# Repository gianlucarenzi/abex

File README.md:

Atari Bus EXtender for Atari XE Computers
=====================================

This is a Atari PBI & ECI Bus extender, for adding expansion board with ease,
called Atari Bus EXtender for Atari XE Computers or ABEX for short.

This project expand somehow the Atari 1090XL Bus Expansion in the early 80s
but with a simple layout and using only 3.3v compliant electronics.
No 5V is available on the bus, and all signals are converted to 3.3v level.

The Bus recall somehow the AteoBus from Amiga 1200 Computers but using a
more common nowadays PCI-Express Bus Slots with 64 pins.

Right now there are 2 boards desinged for this bus:

1- Atari DUO Cart (a porting of the famous Uno-Cart Project)

2- Atari MegaRAM (a PortB PIA Emulator) with 1024K RAM memory banked

More boards can be added as soon they do not interfere with the others
like using the PBI Protocol device in available in ROM. For example a simple
RS232 Board can be designed using a STM32F407 as port EXPANDER with R: handler
in internal flash, or a SDCard Hard Drive Simulator can be designed as well.

Even WiFi or Ethernet Controller can be achived flawlessly.

Everything is up to you, using your mind to open the world to this wonderful
machine like Atari 130XE.

Rendered Images
===============
# Front
# Back
# Overall

Hardware License
================
Copyright (C) 2018/2019 Gianluca Renzi <gianlucarenzi@eurek.it> <icjtqr@gmail.com>

The hardware of this project is released as free/open hardware under the
Creative Commons Attribution Share-Alike license. See `LICENSE.hw` for details.

Firmware License
================
Copyright (C) 2019 Gianluca Renzi <icjtqr@gmail.com>

The microcontroller firmware of this project is released as free software,
under the terms of the GNU General Public License v3, or later.  See
`LICENSE.sw` for details.

Software License
================
The host software (amigafloppy tool) is released as free software, under the
terms of the GNU General Public License v3, or later. See `LICENSE.sw` or licence.txt for
details.

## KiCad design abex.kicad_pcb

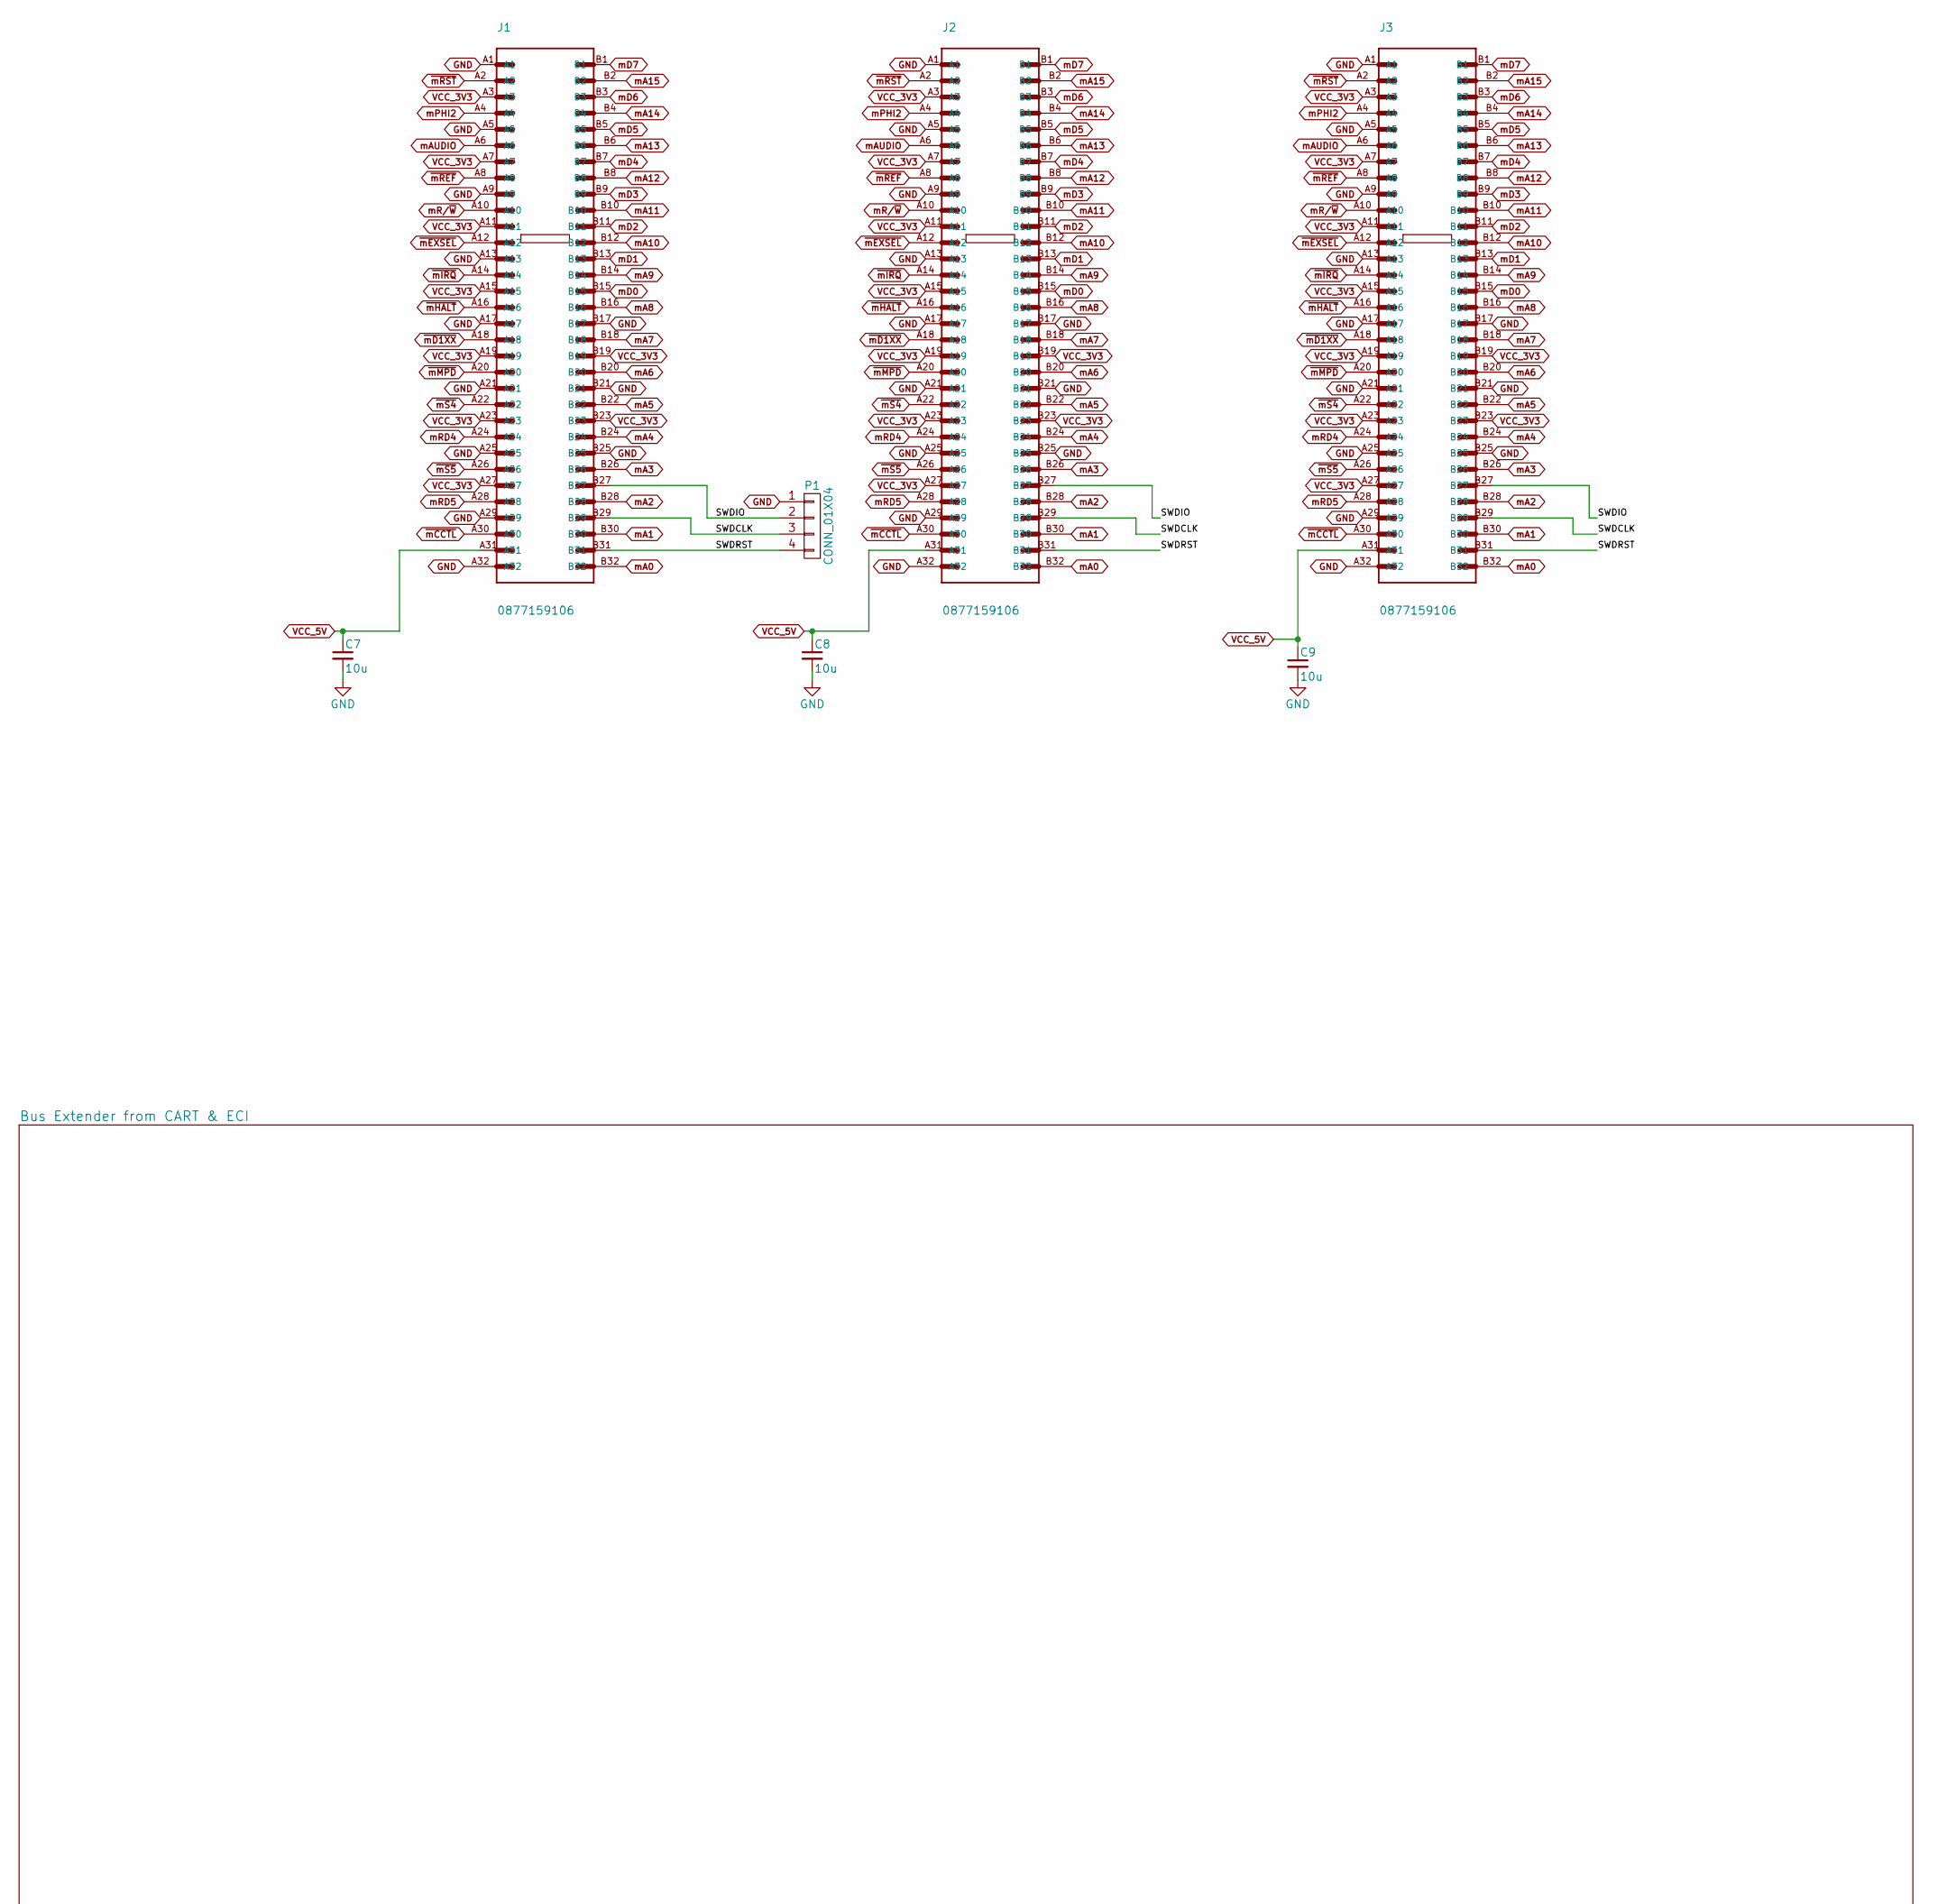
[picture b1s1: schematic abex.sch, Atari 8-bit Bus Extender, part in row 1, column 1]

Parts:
C7, C8, C9: 10u; C_1206_HandSoldering
J1, J2, J3: 0877159106; MOLEX_0877159106
P1: CONN_01X04; Pin_Header_Angled_1x04

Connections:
/SWDCLK: J1.B29, J2.B29, J3.B29, P1.3
/SWDIO: J1.B27, J2.B27, J3.B27, P1.2
/SWDRST: J1.B31, J2.B31, J3.B31, P1.4
GND: C7.2, C8.2, C9.2, J1.A1, J1.A5, J1.A9, J1.A13, J1.A17, J1.A21, J1.A25, J1.A29, J1.A32, J1.B17, J1.B21, J1.B25, J2.A1, J2.A5, J2.A9, J2.A13, J2.A17, J2.A21, J2.A25, J2.A29, J2.A32, J2.B17, J2.B21, J2.B25, J3.A1, J3.A5, J3.A9, J3.A13, J3.A17, J3.A21, J3.A25, J3.A29, J3.A32, J3.B17, J3.B21, J3.B25, P1.1; also elsewhere on the board
VCC_3V3: J1.A3, J1.A7, J1.A11, J1.A15, J1.A19, J1.A23, J1.A27, J1.B19, J1.B23, J2.A3, J2.A7, J2.A11, J2.A15, J2.A19, J2.A23, J2.A27, J2.B19, J2.B23, J3.A3, J3.A7, J3.A11, J3.A15, J3.A19, J3.A23, J3.A27, J3.B19, J3.B23; also elsewhere on the board
VCC_5V: C7.1, C8.1, C9.1, J1.A31, J2.A31, J3.A31; also elsewhere on the board
mA0: J1.B32, J2.B32, J3.B32; also elsewhere on the board
mA1: J1.B30, J2.B30, J3.B30; also elsewhere on the board
mA2: J1.B28, J2.B28, J3.B28; also elsewhere on the board
mA3: J1.B26, J2.B26, J3.B26; also elsewhere on the board
mA4: J1.B24, J2.B24, J3.B24; also elsewhere on the board
mA5: J1.B22, J2.B22, J3.B22; also elsewhere on the board
mA6: J1.B20, J2.B20, J3.B20; also elsewhere on the board
mA7: J1.B18, J2.B18, J3.B18; also elsewhere on the board
mA8: J1.B16, J2.B16, J3.B16; also elsewhere on the board
mA9: J1.B14, J2.B14, J3.B14; also elsewhere on the board
mA10: J1.B12, J2.B12, J3.B12; also elsewhere on the board
mA11: J1.B10, J2.B10, J3.B10; also elsewhere on the board
mA12: J1.B8, J2.B8, J3.B8; also elsewhere on the board
mA13: J1.B6, J2.B6, J3.B6; also elsewhere on the board
mA14: J1.B4, J2.B4, J3.B4; also elsewhere on the board
mA15: J1.B2, J2.B2, J3.B2; also elsewhere on the board
mAUDIO: J1.A6, J2.A6, J3.A6; also elsewhere on the board
mD0: J1.B15, J2.B15, J3.B15; also elsewhere on the board
mD1: J1.B13, J2.B13, J3.B13; also elsewhere on the board
mD2: J1.B11, J2.B11, J3.B11; also elsewhere on the board
mD3: J1.B9, J2.B9, J3.B9; also elsewhere on the board
mD4: J1.B7, J2.B7, J3.B7; also elsewhere on the board
mD5: J1.B5, J2.B5, J3.B5; also elsewhere on the board
mD6: J1.B3, J2.B3, J3.B3; also elsewhere on the board
mD7: J1.B1, J2.B1, J3.B1; also elsewhere on the board
mPHI2: J1.A4, J2.A4, J3.A4; also elsewhere on the board
mR/~W: J1.A10, J2.A10, J3.A10; also elsewhere on the board
mRD4: J1.A24, J2.A24, J3.A24; also elsewhere on the board
mRD5: J1.A28, J2.A28, J3.A28; also elsewhere on the board
~mCCTL: J1.A30, J2.A30, J3.A30; also elsewhere on the board
~mD1XX: J1.A18, J2.A18, J3.A18; also elsewhere on the board
~mEXSEL: J1.A12, J2.A12, J3.A12; also elsewhere on the board
~mHALT: J1.A16, J2.A16, J3.A16; also elsewhere on the board
~mIRQ: J1.A14, J2.A14, J3.A14; also elsewhere on the board
~mMPD: J1.A20, J2.A20, J3.A20; also elsewhere on the board
~mREF: J1.A8, J2.A8, J3.A8; also elsewhere on the board
~mRST: J1.A2, J2.A2, J3.A2; also elsewhere on the board
~mS4: J1.A22, J2.A22, J3.A22; also elsewhere on the board
~mS5: J1.A26, J2.A26, J3.A26; also elsewhere on the board

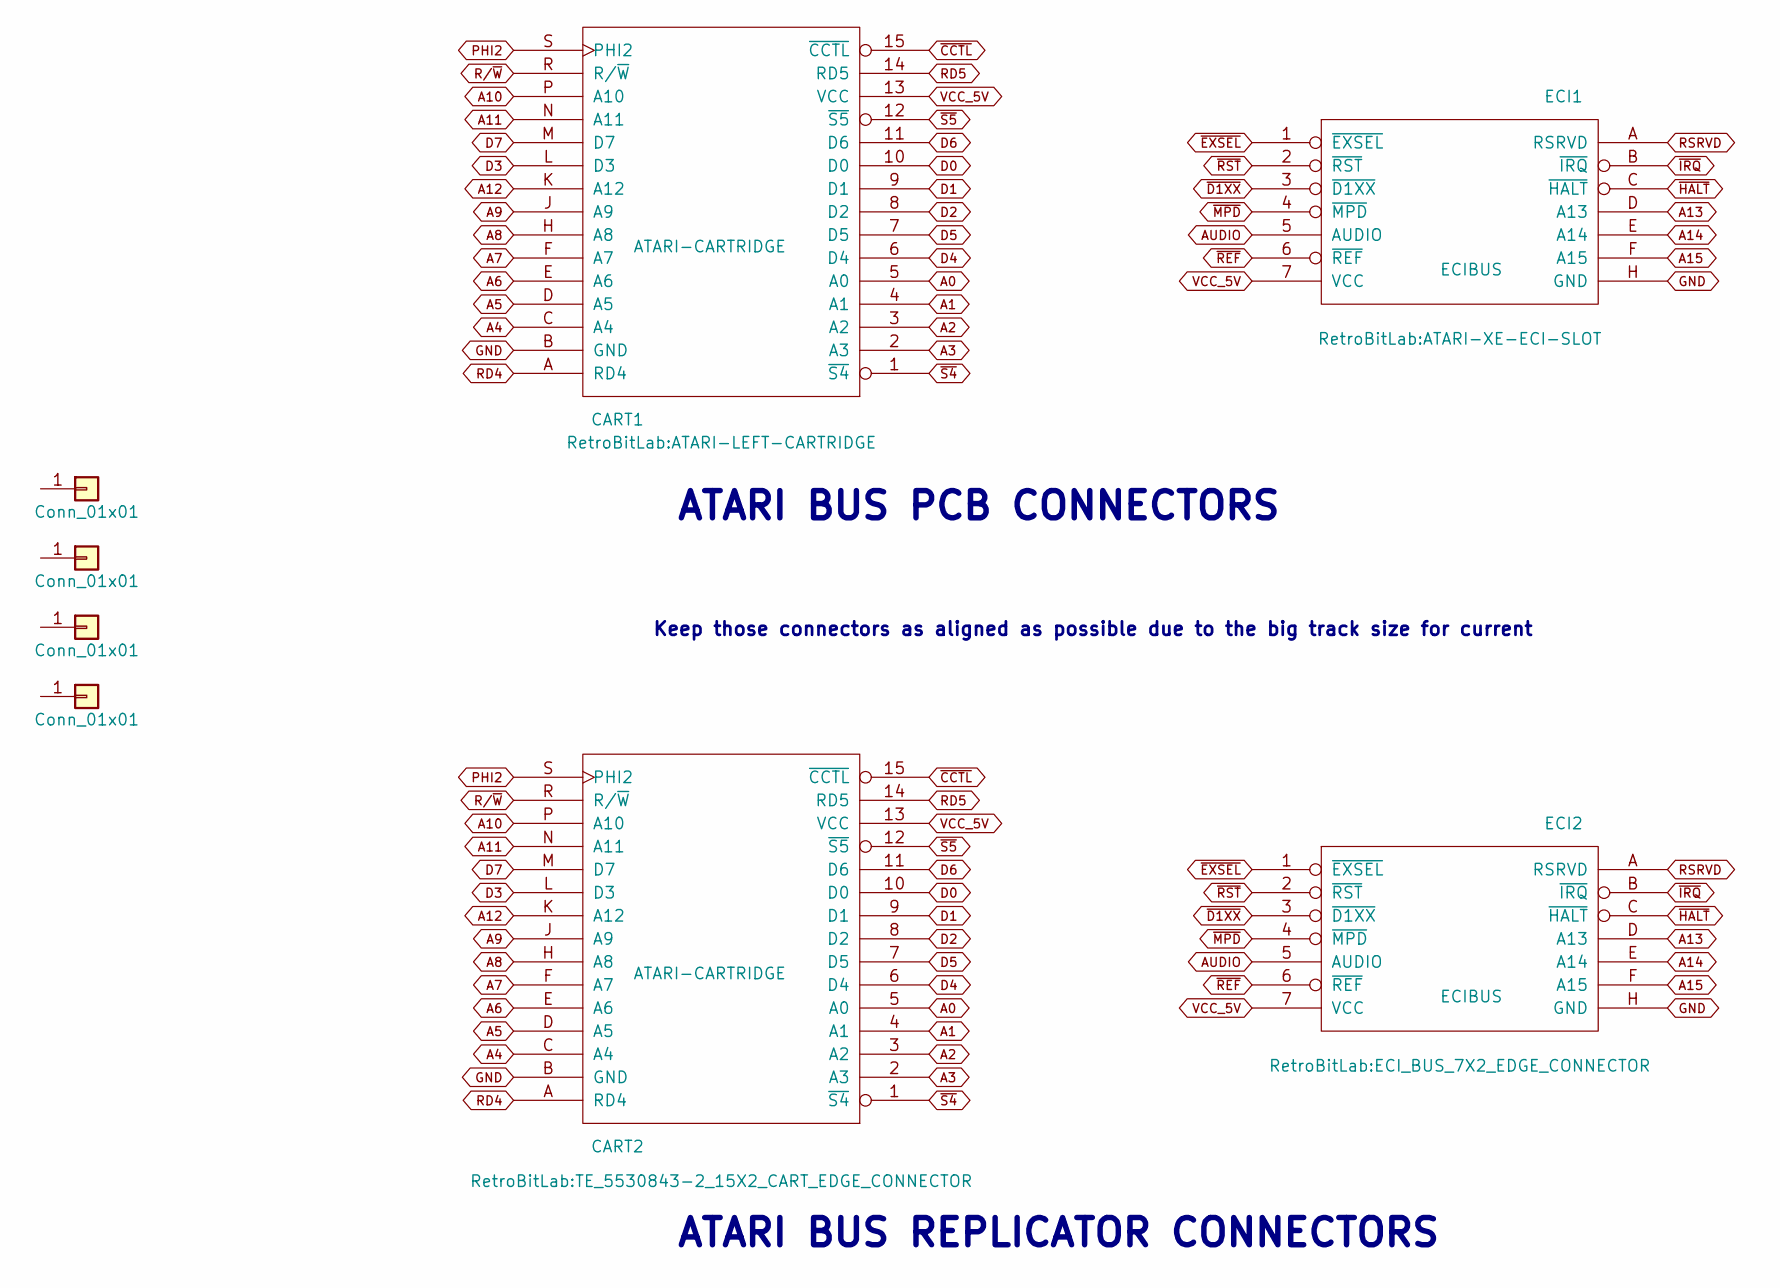
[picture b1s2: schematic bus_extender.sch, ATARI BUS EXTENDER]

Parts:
CART1: ATARI-CARTRIDGE; ATARI-LEFT-CARTRIDGE
CART2: ATARI-CARTRIDGE; TE_5530843-2_15X2_CART_EDGE_CONNECTOR
ECI1: ECIBUS; ATARI-XE-ECI-SLOT
ECI2: ECIBUS; ECI_BUS_7X2_EDGE_CONNECTOR
J4, J5, J6, J7: Conn_01x01; MountingHole_3mm

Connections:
A0: CART1.5 (A0), CART2.5 (A0); also elsewhere on the board
A1: CART1.4 (A1), CART2.4 (A1); also elsewhere on the board
A2: CART1.3 (A2), CART2.3 (A2); also elsewhere on the board
A3: CART1.2 (A3), CART2.2 (A3); also elsewhere on the board
A4: CART1.C (A4), CART2.C (A4); also elsewhere on the board
A5: CART1.D (A5), CART2.D (A5); also elsewhere on the board
A6: CART1.E (A6), CART2.E (A6); also elsewhere on the board
A7: CART1.F (A7), CART2.F (A7); also elsewhere on the board
A8: CART1.H (A8), CART2.H (A8); also elsewhere on the board
A9: CART1.J (A9), CART2.J (A9); also elsewhere on the board
A10: CART1.P (A10), CART2.P (A10); also elsewhere on the board
A11: CART1.N (A11), CART2.N (A11); also elsewhere on the board
A12: CART1.K (A12), CART2.K (A12); also elsewhere on the board
A13: ECI1.D (A13), ECI2.D (A13); also elsewhere on the board
A14: ECI1.E (A14), ECI2.E (A14); also elsewhere on the board
A15: ECI1.F (A15), ECI2.F (A15); also elsewhere on the board
AUDIO: ECI1.5 (AUDIO), ECI2.5 (AUDIO); also elsewhere on the board
D0: CART1.10 (D0), CART2.10 (D0); also elsewhere on the board
D1: CART1.9 (D1), CART2.9 (D1); also elsewhere on the board
D2: CART1.8 (D2), CART2.8 (D2); also elsewhere on the board
D3: CART1.L (D3), CART2.L (D3); also elsewhere on the board
D4: CART1.6 (D4), CART2.6 (D4); also elsewhere on the board
D5: CART1.7 (D5), CART2.7 (D5); also elsewhere on the board
D6: CART1.11 (D6), CART2.11 (D6); also elsewhere on the board
D7: CART1.M (D7), CART2.M (D7); also elsewhere on the board
GND: CART1.B (GND), CART2.B (GND), ECI1.H (GND), ECI2.H (GND); also elsewhere on the board
PHI2: CART1.S (PHI2), CART2.S (PHI2); also elsewhere on the board
R/~W: CART1.R (R/~W), CART2.R (R/~W); also elsewhere on the board
RD4: CART1.A (RD4), CART2.A (RD4); also elsewhere on the board
RD5: CART1.14 (RD5), CART2.14 (RD5); also elsewhere on the board
RSRVD: ECI1.A (RSRVD), ECI2.A (RSRVD)
VCC_5V: CART1.13 (VCC), CART2.13 (VCC), ECI1.7 (VCC), ECI2.7 (VCC); also elsewhere on the board
~CCTL: CART1.15 (~CCTL), CART2.15 (~CCTL); also elsewhere on the board
~D1XX: ECI1.3 (~D1XX), ECI2.3 (~D1XX); also elsewhere on the board
~EXSEL: ECI1.1 (~EXSEL), ECI2.1 (~EXSEL); also elsewhere on the board
~HALT: ECI1.C (~HALT), ECI2.C (~HALT); also elsewhere on the board
~IRQ: ECI1.B (~IRQ), ECI2.B (~IRQ); also elsewhere on the board
~MPD: ECI1.4 (~MPD), ECI2.4 (~MPD); also elsewhere on the board
~REF: ECI1.6 (~REF), ECI2.6 (~REF); also elsewhere on the board
~RST: ECI1.2 (~RST), ECI2.2 (~RST); also elsewhere on the board
~S4: CART1.1 (~S4), CART2.1 (~S4); also elsewhere on the board
~S5: CART1.12 (~S5), CART2.12 (~S5); also elsewhere on the board

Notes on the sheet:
ATARI BUS PCB CONNECTORS
ATARI BUS REPLICATOR CONNECTORS
Keep those connectors as aligned as possible due to the big track size for current

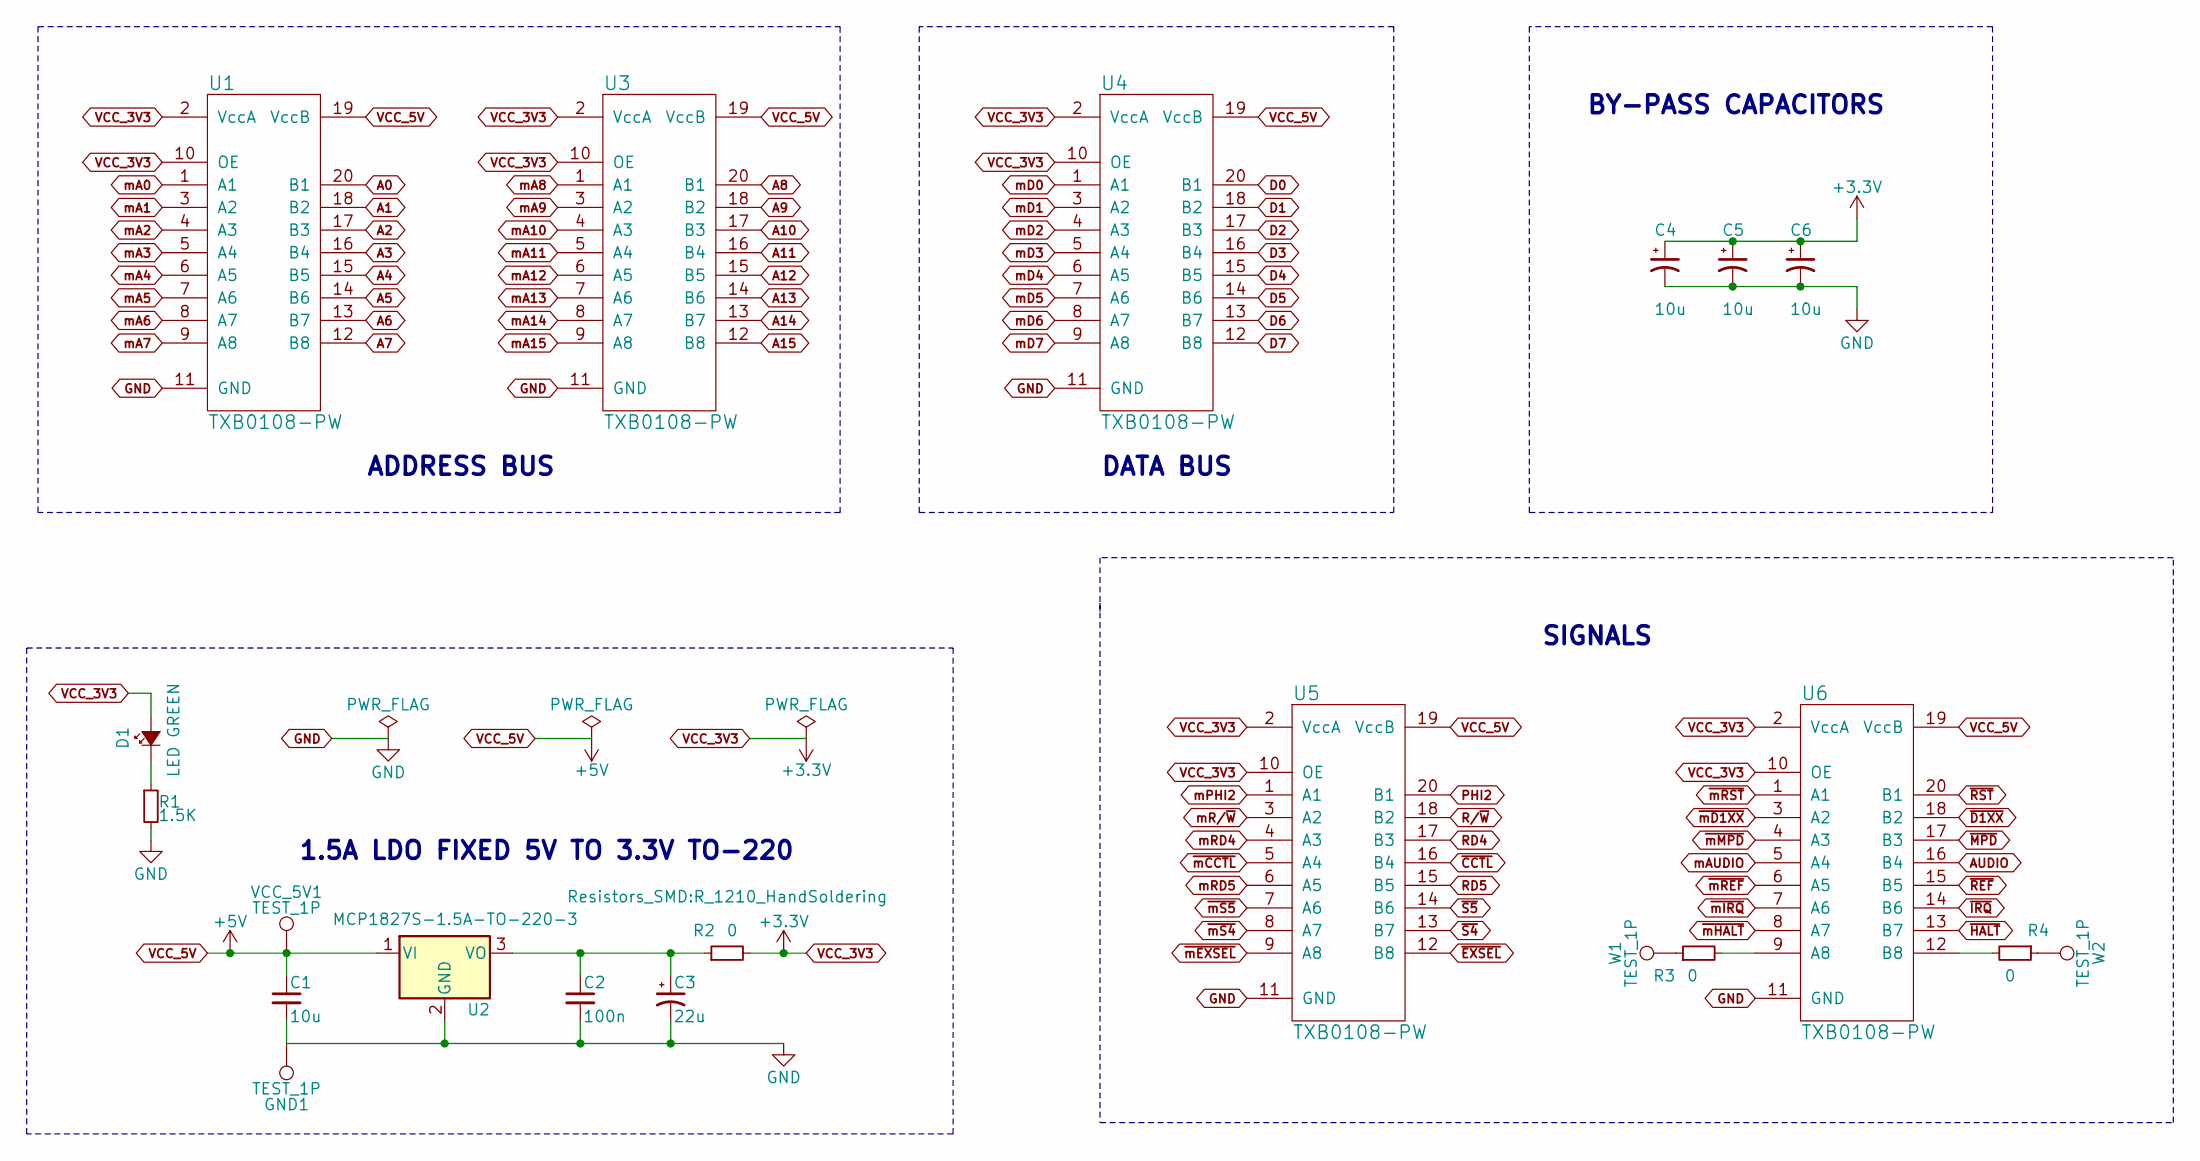
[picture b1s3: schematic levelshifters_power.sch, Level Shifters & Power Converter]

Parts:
C1: 10u; C_1206_HandSoldering
C2: 100n; C_1206_HandSoldering
C3: 22u; TantalC_SizeA_EIA-3216_HandSoldering
C4, C5, C6: 10u; CP_Radial_D10.0mm_P2.50mm_3D
D1: LED GREEN; LED_1206
GND1: TEST_1P; Pin_Header_Straight_1x01
R1: 1.5K; R_1210_HandSoldering
R2, R3, R4: 0; R_1210_HandSoldering
U1, U3, U4, U5, U6: TXB0108-PW; SSOP-20_4.4x6.5mm_Pitch0.65mm
U2: MCP1827S-1.5A-TO-220-3; MCP_1827S_TO-220-3_Horizontal_TabDown
VCC_5V1: TEST_1P; Pin_Header_Straight_1x01
W1, W2: TEST_1P; Pin_Header_Straight_1x01

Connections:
A0: U1.20 (B1); also elsewhere on the board
A1: U1.18 (B2); also elsewhere on the board
A2: U1.17 (B3); also elsewhere on the board
A3: U1.16 (B4); also elsewhere on the board
A4: U1.15 (B5); also elsewhere on the board
A5: U1.14 (B6); also elsewhere on the board
A6: U1.13 (B7); also elsewhere on the board
A7: U1.12 (B8); also elsewhere on the board
A8: U3.20 (B1); also elsewhere on the board
A9: U3.18 (B2); also elsewhere on the board
A10: U3.17 (B3); also elsewhere on the board
A11: U3.16 (B4); also elsewhere on the board
A12: U3.15 (B5); also elsewhere on the board
A13: U3.14 (B6); also elsewhere on the board
A14: U3.13 (B7); also elsewhere on the board
A15: U3.12 (B8); also elsewhere on the board
AUDIO: U6.16 (B4); also elsewhere on the board
D0: U4.20 (B1); also elsewhere on the board
D1: U4.18 (B2); also elsewhere on the board
D2: U4.17 (B3); also elsewhere on the board
D3: U4.16 (B4); also elsewhere on the board
D4: U4.15 (B5); also elsewhere on the board
D5: U4.14 (B6); also elsewhere on the board
D6: U4.13 (B7); also elsewhere on the board
D7: U4.12 (B8); also elsewhere on the board
GND: C1.2, C2.2, C3.2, C4.2, C5.2, C6.2, GND1.1, R1.2, U1.11 (GND), U2.2 (GND), U3.11 (GND), U4.11 (GND), U5.11 (GND), U6.11 (GND); also elsewhere on the board
unnamed: C2.1, C3.1, R2.1, U2.3 (VO)
unnamed: D1.1 (K), R1.1
unnamed: R3.1, W1.1
unnamed: R3.2, U6.9 (A8)
unnamed: R4.1, W2.1
unnamed: R4.2, U6.12 (B8)
PHI2: U5.20 (B1); also elsewhere on the board
R/~W: U5.18 (B2); also elsewhere on the board
RD4: U5.17 (B3); also elsewhere on the board
RD5: U5.15 (B5); also elsewhere on the board
VCC_3V3: C4.1, C5.1, C6.1, D1.2 (A), R2.2, U1.2 (VccA), U1.10 (OE), U3.2 (VccA), U3.10 (OE), U4.2 (VccA), U4.10 (OE), U5.2 (VccA), U5.10 (OE), U6.2 (VccA), U6.10 (OE); also elsewhere on the board
VCC_5V: C1.1, U1.19 (VccB), U2.1 (VI), U3.19 (VccB), U4.19 (VccB), U5.19 (VccB), U6.19 (VccB), VCC_5V1.1; also elsewhere on the board
mA0: U1.1 (A1); also elsewhere on the board
mA1: U1.3 (A2); also elsewhere on the board
mA2: U1.4 (A3); also elsewhere on the board
mA3: U1.5 (A4); also elsewhere on the board
mA4: U1.6 (A5); also elsewhere on the board
mA5: U1.7 (A6); also elsewhere on the board
mA6: U1.8 (A7); also elsewhere on the board
mA7: U1.9 (A8); also elsewhere on the board
mA8: U3.1 (A1); also elsewhere on the board
mA9: U3.3 (A2); also elsewhere on the board
mA10: U3.4 (A3); also elsewhere on the board
mA11: U3.5 (A4); also elsewhere on the board
mA12: U3.6 (A5); also elsewhere on the board
mA13: U3.7 (A6); also elsewhere on the board
mA14: U3.8 (A7); also elsewhere on the board
mA15: U3.9 (A8); also elsewhere on the board
mAUDIO: U6.5 (A4); also elsewhere on the board
mD0: U4.1 (A1); also elsewhere on the board
mD1: U4.3 (A2); also elsewhere on the board
mD2: U4.4 (A3); also elsewhere on the board
mD3: U4.5 (A4); also elsewhere on the board
mD4: U4.6 (A5); also elsewhere on the board
mD5: U4.7 (A6); also elsewhere on the board
mD6: U4.8 (A7); also elsewhere on the board
mD7: U4.9 (A8); also elsewhere on the board
mPHI2: U5.1 (A1); also elsewhere on the board
mR/~W: U5.3 (A2); also elsewhere on the board
mRD4: U5.4 (A3); also elsewhere on the board
mRD5: U5.6 (A5); also elsewhere on the board
~CCTL: U5.16 (B4); also elsewhere on the board
~D1XX: U6.18 (B2); also elsewhere on the board
~EXSEL: U5.12 (B8); also elsewhere on the board
~HALT: U6.13 (B7); also elsewhere on the board
~IRQ: U6.14 (B6); also elsewhere on the board
~MPD: U6.17 (B3); also elsewhere on the board
~REF: U6.15 (B5); also elsewhere on the board
~RST: U6.20 (B1); also elsewhere on the board
~S4: U5.13 (B7); also elsewhere on the board
~S5: U5.14 (B6); also elsewhere on the board
~mCCTL: U5.5 (A4); also elsewhere on the board
~mD1XX: U6.3 (A2); also elsewhere on the board
~mEXSEL: U5.9 (A8); also elsewhere on the board
~mHALT: U6.8 (A7); also elsewhere on the board
~mIRQ: U6.7 (A6); also elsewhere on the board
~mMPD: U6.4 (A3); also elsewhere on the board
~mREF: U6.6 (A5); also elsewhere on the board
~mRST: U6.1 (A1); also elsewhere on the board
~mS4: U5.8 (A7); also elsewhere on the board
~mS5: U5.7 (A6); also elsewhere on the board

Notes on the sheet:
1.5A LDO FIXED 5V TO 3.3V TO-220
ADDRESS BUS
DATA BUS
SIGNALS
BY-PASS CAPACITORS

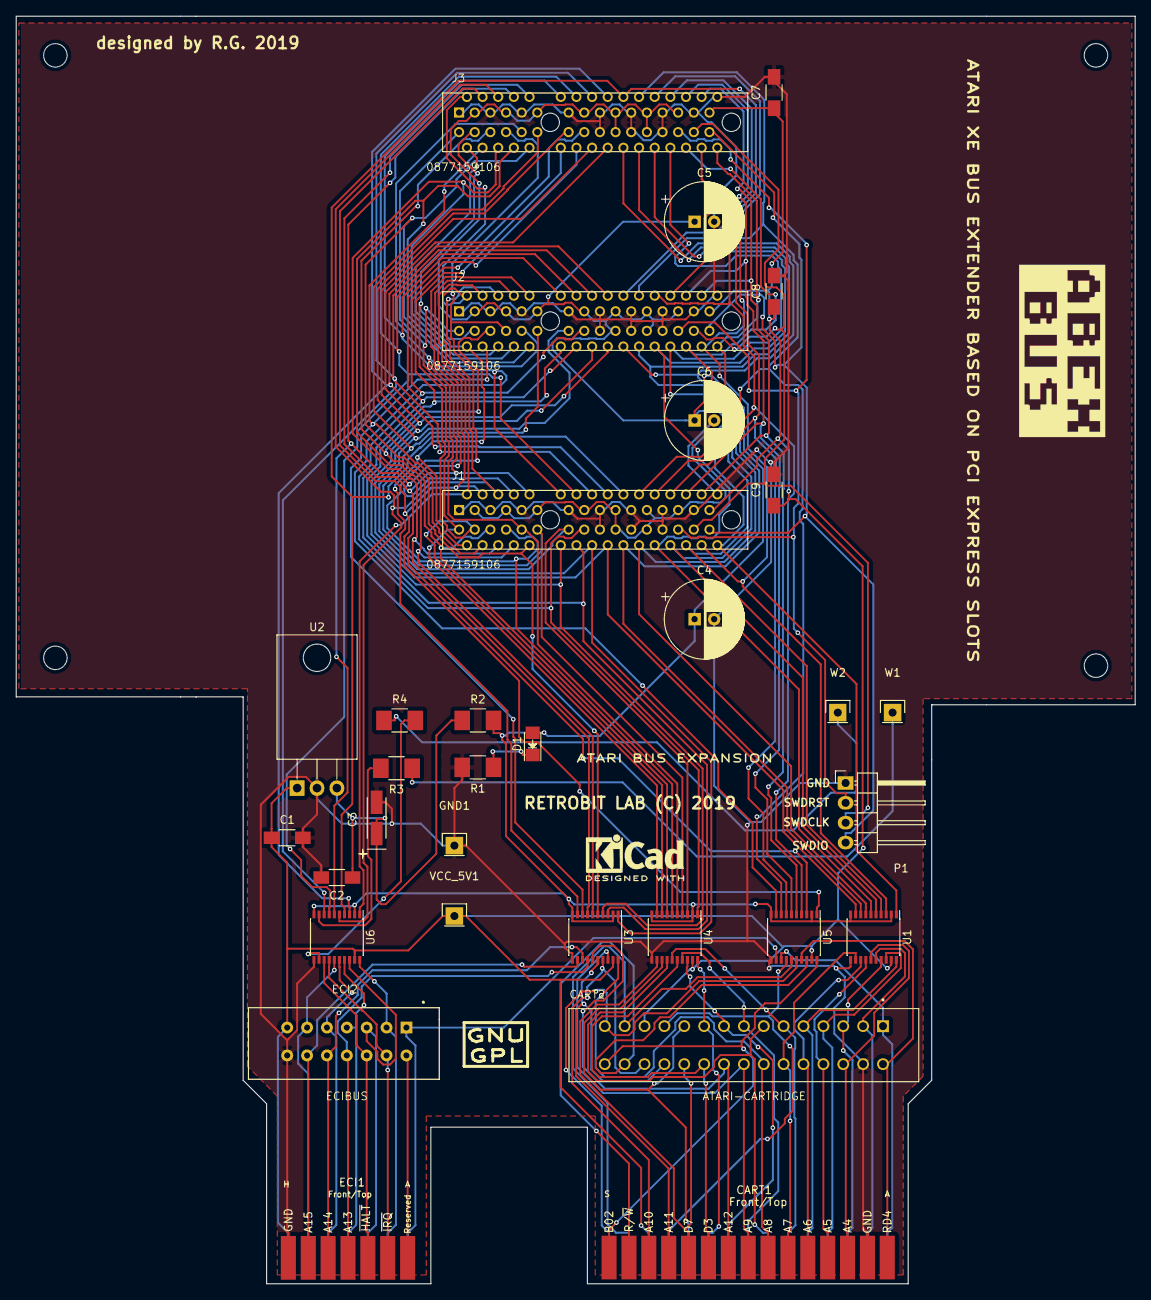
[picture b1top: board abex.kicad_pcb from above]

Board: 2 copper layers, 143.0 x 162.0 mm, 39 parts (1 on the bottom side), 91 nets.

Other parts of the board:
ATARILOGO: LOGO; atari_fuji_SilkScreen_21.2x25-Rev
GPL: Symbol_GNU-GPL_CopperTop_Small; Symbol_GNU-GPL_SilkScreen_Small
LOGO: LOGO; ABEX_Logo_22mmx11mm_WB

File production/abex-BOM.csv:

"Id";"Designator";"Package";"Quantity";"Designation";"Supplier and ref";
1;"REF**";"KiCad-Logo2_5mm_SilkScreen";1;"KiCad-Logo2_5mm_SilkScreen";;;
2;"GPL";"Symbol_GNU-GPL_SilkScreen_Small";1;"Symbol_GNU-GPL_CopperTop_Small";;;
3;"LOGO";"ABEX_Logo_22mmx11mm_WB";1;"LOGO";;;
4;"C1,C7,C8,C9";"C_1206_HandSoldering";4;"10u";;;
5;"C2";"C_1206_HandSoldering";1;"100n";;;
6;"C3";"TantalC_SizeA_EIA-3216_HandSoldering";1;"22u";;;
7;"CART1";"ATARI-LEFT-CARTRIDGE";1;"ATARI-CARTRIDGE";;;
8;"CART2";"TE_5530843-2_15X2_CART_EDGE_CONNECTOR";1;"ATARI-CARTRIDGE";;;
9;"D1";"LED_1206";1;"LED GREEN";;;
10;"ECI1";"ATARI-XE-ECI-SLOT";1;"ECIBUS";;;
11;"R1";"R_1210_HandSoldering";1;"1.5K";;;
12;"R2,R4,R3";"R_1210_HandSoldering";3;"0";;;
13;"U1,U3,U4,U5,U6";"SSOP-20_4.4x6.5mm_Pitch0.65mm";5;"TXB0108-PW";;;
14;"W1,W2,GND1,VCC_5V1";"Pin_Header_Straight_1x01";4;"TEST_1P";;;
15;"J4,J5,J6,J7";"MountingHole_3mm";4;"Conn_01x01";;;
16;"ECI2";"ECI_BUS_7X2_EDGE_CONNECTOR";1;"ECIBUS";;;
17;"P1";"Pin_Header_Angled_1x04";1;"CONN_01X04";;;
18;"C4,C5,C6";"CP_Radial_D10.0mm_P2.50mm_3D";3;"10u";;;
19;"U2";"MCP_1827S_TO-220-3_Horizontal_TabDown";1;"MCP1827S-1.5A-TO-220-3";;;
20;"J1,J2,J3";"MOLEX_0877159106";3;"0877159106";;;
21;"ATARILOGO";"atari_fuji_SilkScreen_21.2x25-Rev";1;"LOGO";;;

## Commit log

2019-05-25 First import
2019-06-07 Missing NPTH???
2019-06-07 Changed the GPL logo footprint.
2019-06-27 Added +5VDC on connector (pin 31). All data & bus signals remain 3.3V tolerant.
    Added +5VDC on connector (pin 31). All data & bus signals remain 3.3V
    tolerant. If a card need to have 5V signals it need to have all level
    shifters needed on board.
2025-11-01 RetroBitLab library

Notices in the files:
abex.kicad_pcb:
RETROBIT LAB (C) 2019
